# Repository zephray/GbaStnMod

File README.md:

# License

The hardware design is released under the CERN Open Source Hardware License strongly-reciprocal variant, CERN-OHL-S. A copy of the license is provided in the source repository. Additionally, user guide of the license is provided on ohwr.org.

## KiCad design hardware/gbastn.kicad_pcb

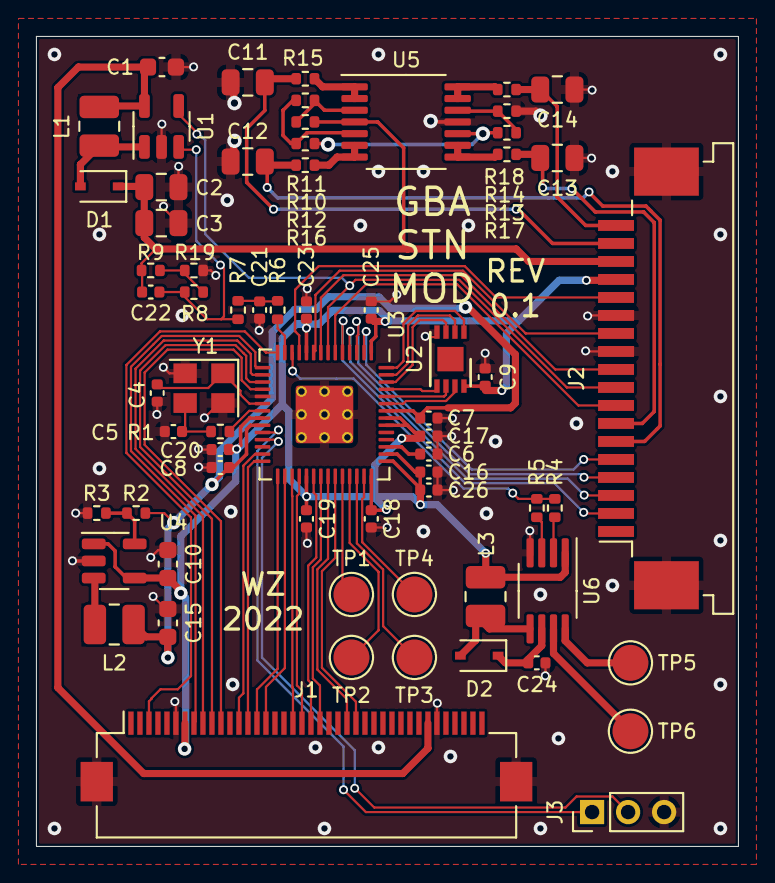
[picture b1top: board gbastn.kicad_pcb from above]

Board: 2 copper layers, 39.0 x 45.0 mm, 66 parts (0 on the bottom side), 71 nets.

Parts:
C1, C10, C15: 10uF; C_0603_1608Metric
C2, C3, C11, C12, C13, C14: 4.7uF/25V; C_0805_2012Metric
C4, C5: 18pF; C_0402_1005Metric
C6, C16, C21: 1uF; C_0402_1005Metric
C7, C8, C9, C17, C18, C19, C20, C23, C25, C26: 100nF; C_0402_1005Metric
C22: 220pF; C_0402_1005Metric
C24: 3.3nF/100V; C_0402_1005Metric
D1, D2: MBR0530; D_SOD-323
J1: Conn_01x40_MountingPin; Hirose_FH12-40S-0.5SH_1x40-1MP_P0.50mm_Horizontal
J2: Conn_01x18_MountingPin; TE_1-84953-8_1x18-1MP_P1.0mm_Horizontal
J3: Conn_01x03; PinHeader_1x03_P2.00mm_Vertical
L1: 10uH; L_1008_2520Metric
L2: 4.7uH; L_1008_2520Metric
L3: 220uH; L_1008_2520Metric
R1: 1K; R_0402_1005Metric
R2, R3, R6, R10, R11, R13, R14: 10K; R_0402_1005Metric
R4: 560K; R_0402_1005Metric
R5: 2M; R_0402_1005Metric
R7: 47K; R_0402_1005Metric
R8: 4.7K; R_0402_1005Metric
R9: 330K/1%; R_0402_1005Metric
R12: 75K; R_0402_1005Metric
R15, R16, R17, R18: 10; R_0402_1005Metric
R19: 18K/1%; R_0402_1005Metric
TP1, TP2, TP3, TP4, TP5, TP6: TestPoint; TestPoint_Pad_D2.0mm
U1: AP3015; TSOT-23-5
U2: FM25Q04-DN-T-G; DFN-8-1EP_3x2mm_P0.5mm_EP1.36x1.46mm
U3: RP2040; RP2040-QFN-56
U4: SY8008; TSOT-23-5
U5: LM324; TSSOP-14_4.4x5mm_P0.65mm
U6: HV857; MSOP-8_3x3mm_P0.65mm
Y1: 12MHz; Oscillator_SMD_Abracon_ASE-4Pin_3.2x2.5mm

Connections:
+1V1: C6.1, U3.45 (VREG_VOUT)
+1V2: C7.1, C8.1, C15.2, L2.2, R2.2, U3.23 (DVDD), U3.50 (DVDD)
+3V3: C9.1, C10.2, C16.1, C17.1, C18.1, C19.1, C20.1, C23.1, C25.1, C26.1, J1.7, J2.15, L3.1, U2.8 (VCC), U3.1 (IOVDD), U3.10 (IOVDD), U3.22 (IOVDD), U3.33 (IOVDD), U3.42 (IOVDD), U3.43 (ADC_AVDD), U3.44 (VREG_IN), U3.48 (USB_VDD), U3.49 (IOVDD), U4.1 (RUN), U4.4 (VIN), U6.1 (VDD)
+5V: C1.2, J1.34, L1.1, U1.5 (VIN)
/AC: J2.10, U3.8 (GPIO6)
/BL_EN: R4.2, R5.2, U3.12 (GPIO9)
/BTN_L: TP3.1, U3.40 (GPIO28_ADC2)
/BTN_R: TP4.1, U3.41 (GPIO29_ADC3)
/BTN_SEL: TP2.1, U3.39 (GPIO27_ADC1)
/BTN_START: TP1.1, U3.38 (GPIO26_ADC0)
/D0: J2.2, U3.5 (GPIO3)
/D1: J2.3, U3.4 (GPIO2)
/D2: J2.4, U3.3 (GPIO1)
/D3: J2.5, U3.2 (GPIO0)
/ELA: TP5.1, U6.8 (VA)
/ELB: TP6.1, U6.7 (VB)
/GBA_B2: J1.22, U3.35 (GPIO23)
/GBA_B3: J1.21, U3.34 (GPIO22)
/GBA_B4: J1.20, U3.32 (GPIO21)
/GBA_B5: J1.19, U3.31 (GPIO20)
/GBA_G2: J1.16, U3.30 (GPIO19)
/GBA_G3: J1.15, U3.29 (GPIO18)
/GBA_G4: J1.14, U3.28 (GPIO17)
/GBA_G5: J1.13, U3.27 (GPIO16)
/GBA_HS: J1.25, U3.36 (GPIO24)
/GBA_R2: J1.11, U3.18 (GPIO15)
/GBA_R3: J1.10, U3.17 (GPIO14)
/GBA_R4: J1.9, U3.16 (GPIO13)
/GBA_R5: J1.8, U3.15 (GPIO12)
/GBA_VS: J1.26, U3.37 (GPIO25)
/GBA_XCK: J1.3, U3.14 (GPIO11)
/HSYNC: J2.12, U3.9 (GPIO7)
/LCD_EN: J2.9, U1.4 (RUN), U3.7 (GPIO5)
/LCD_V1: C11.2, J2.17, R15.1
/LCD_V2: C12.2, J2.6, R16.1
/LCD_V3: C13.2, J2.7, R17.1
/LCD_V4: C14.2, J2.18, R18.1
/QSPI_SCLK: U2.6 (CLK), U3.52 (QSPI_SCLK)
/QSPI_SD0: U2.5 (DI(IO0)), U3.53 (QSPI_SD0)
/QSPI_SD1: U2.2 (DO(IO1)), U3.55 (QSPI_SD1)
/QSPI_SD2: U2.3 (IO2), U3.54 (QSPI_SD2)
/QSPI_SD3: U2.7 (IO3), U3.51 (QSPI_SD3)
/QSPI_SS: U2.1 (~CS), U3.56 (QSPI_SS)
/SWCLK: J3.1, U3.24 (SWCLK)
/SWD: J3.2, U3.25 (SWD)
/VCLK: J2.8, U3.6 (GPIO4)
/VPP_PWM: R6.2, U3.13 (GPIO10)
/VSYNC: J2.14, U3.11 (GPIO8)
/XIN: C4.1, U3.20 (XIN), Y1.1
/XOUT: R1.1, U3.21 (XOUT)
GND: C1.1, C2.1, C3.1, C4.2, C5.2, C6.2, C7.2, C8.2, C9.2, C10.1, C11.1, C12.1, C13.1, C14.1, C15.1, C16.2, C17.2, C18.2, C19.2, C20.2, C21.1, C23.2, C24.2, C25.2, C26.2, J1.6, J1.35, J1.MP (MountPin), J2.11, J2.13, J2.MP (MountPin), J3.3, R3.1, R14.2, R19.2, U1.2 (GND), U2.4 (GND), U3.19 (TESTEN), U3.57 (GND), U4.2 (GND), U5.11 (V-), U6.4 (GND), Y1.2, Y1.4
unnamed: C5.1, R1.2, Y1.3
unnamed: C21.2, R6.1, R7.2
unnamed: C24.1, D2.1 (K), U6.6 (CS)
unnamed: D1.2 (A), L1.2, U1.1 (LX)
unnamed: D2.2 (A), L3.2, U6.5 (LX)
unnamed: L2.1, U4.3 (SW)
unnamed: R2.1, R3.2, U4.5 (FB)
unnamed: R4.1, U6.2 (RSW-Osc)
unnamed: R5.1, U6.3 (REL-Osc)
unnamed: R10.2, R11.1, U5.3 (+)
unnamed: R11.2, R12.1, U5.5 (+)
unnamed: R12.2, R13.1, U5.10 (+)
unnamed: R13.2, R14.1, U5.12 (+)
unnamed: R15.2, U5.1, U5.2 (-)
unnamed: R16.2, U5.6 (-), U5.7
unnamed: R17.2, U5.8, U5.9 (-)
unnamed: R18.2, U5.13 (-), U5.14
unnamed: R8.1, R9.1, R19.1
unnamed: C22.1, R7.1, R8.2, U1.3 (FB)
VPP: C2.2, C3.2, C22.2, D1.1 (K), J2.16, R9.2, R10.1, U5.4 (V+)

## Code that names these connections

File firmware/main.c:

//
// Copyright 2021 Wenting Zhang <zephray@outlook.com>
//
// Permission is hereby granted, free of charge, to any person obtaining a copy
// of this software and associated documentation files (the "Software"), to deal
// in the Software without restriction, including without limitation the rights
// to use, copy, modify, merge, publish, distribute, sublicense, and/or sell
// copies of the Software, and to permit persons to whom the Software is
// furnished to do so, subject to the following conditions:
//
// The above copyright notice and this permission notice shall be included in
// all copies or substantial portions of the Software.
//
// THE SOFTWARE IS PROVIDED "AS IS", WITHOUT WARRANTY OF ANY KIND, EXPRESS OR
// IMPLIED, INCLUDING BUT NOT LIMITED TO THE WARRANTIES OF MERCHANTABILITY,
// FITNESS FOR A PARTICULAR PURPOSE AND NONINFRINGEMENT. IN NO EVENT SHALL THE
// AUTHORS OR COPYRIGHT HOLDERS BE LIABLE FOR ANY CLAIM, DAMAGES OR OTHER
// LIABILITY, WHETHER IN AN ACTION OF CONTRACT, TORT OR OTHERWISE, ARISING FROM,
// OUT OF OR IN CONNECTION WITH THE SOFTWARE OR THE USE OR OTHER DEALINGS IN THE
// SOFTWARE.
//
#include <stdio.h>
#include <string.h>
#include "pico/stdlib.h"
#include "pico/multicore.h"
#include "hardware/pwm.h"
#include "hardware/vreg.h"
#include "lcd.h" // For resolution definition, should not call any functions
#include "core1.h"
#include "font.h"
#include "vin.h"

//#define USE_LUT

// Overclock
#define VREG_VSEL   VREG_VOLTAGE_1_20
#define SYSCLK_KHZ  200000

uint8_t contrast = 165;

#define BTN_START 27
#define BTN_SEL 28
#define BTN_L 29
#define BTN_R 26

void set_contrast(uint8_t val) {
    uint slice_num = pwm_gpio_to_slice_num(10);
    pwm_set_chan_level(slice_num, PWM_CHAN_A, val);
}

void update_contrast() {
    static uint8_t cntr = 0;
    if (cntr != 0) {
        cntr--;
        return;
    }
    else {
        cntr = 2;
    }
    if (gpio_get(BTN_START) == false) {
        if (gpio_get(BTN_L) == false) {
            contrast++;
            set_contrast(contrast);
        }
        else if (gpio_get(BTN_R) == false) {
            contrast--;
            set_contrast(contrast);
        }
    }
}

int main()
{
    vreg_set_voltage(VREG_VSEL);
	sleep_ms(10);
    set_sys_clock_khz(SYSCLK_KHZ, true);

    multicore_launch_core1(core1_entry);
    uint32_t g = multicore_fifo_pop_blocking();

    //gpio_put(LED_PIN, 0);
    //sleep_ms(250);

    /*gpio_init(10);
    gpio_set_dir(10, GPIO_OUT);
    gpio_put(10, 0);*/

    gpio_set_function(10, GPIO_FUNC_PWM);
    uint slice_num = pwm_gpio_to_slice_num(10);
    pwm_set_clkdiv(slice_num, 10.0f);
    pwm_set_wrap(slice_num, 255);
    pwm_set_chan_level(slice_num, PWM_CHAN_A, contrast);
    pwm_set_enabled(slice_num, true);

    for (int i = 26; i <= 29; i++) {
        gpio_init(i);
        gpio_set_dir(i, GPIO_IN);
        gpio_pull_up(i);
    }

    gpio_init(9);
    gpio_set_dir(9, GPIO_OUT);
    gpio_put(9, 0);

    vin_init();
    vin_run();

    return 0;
}

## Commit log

2022-11-15 Initial firmware
